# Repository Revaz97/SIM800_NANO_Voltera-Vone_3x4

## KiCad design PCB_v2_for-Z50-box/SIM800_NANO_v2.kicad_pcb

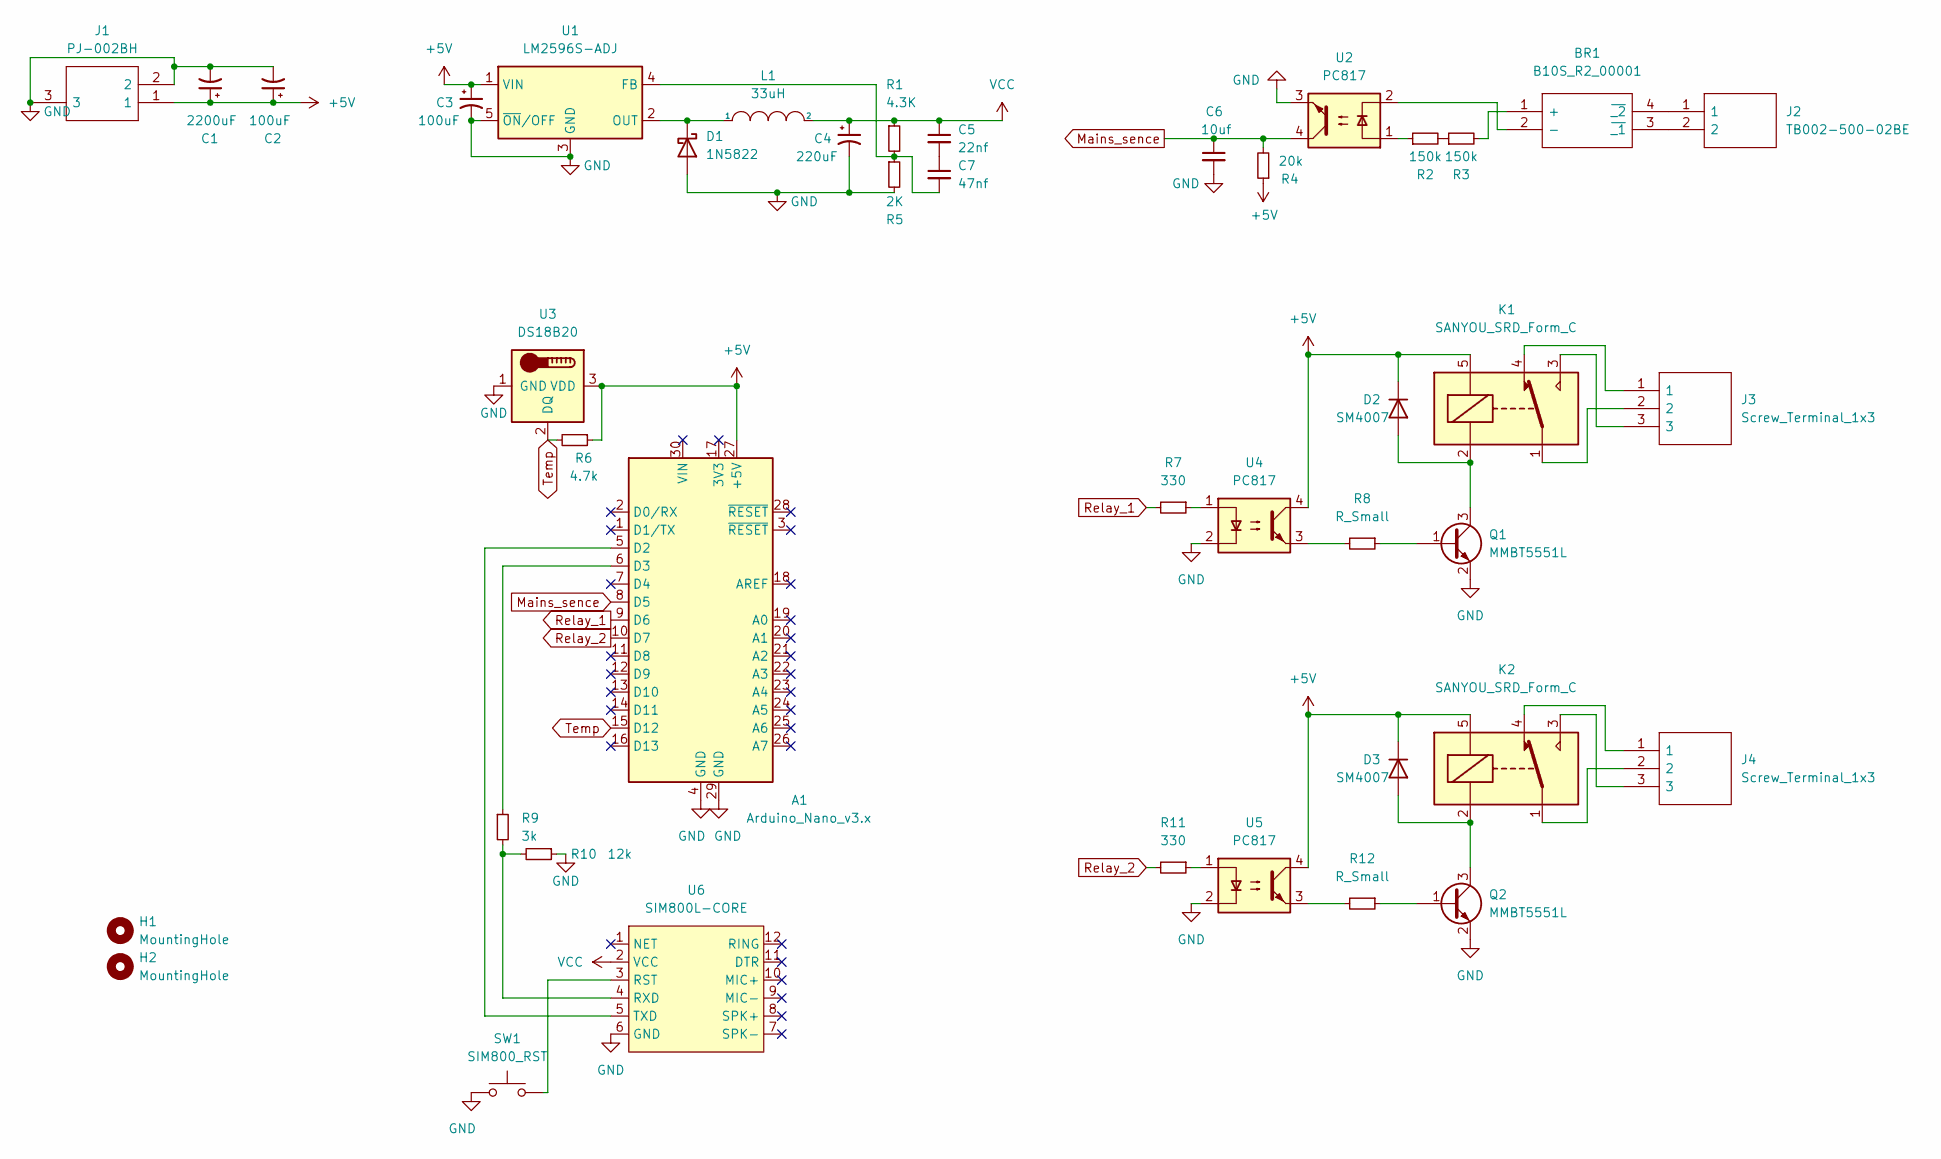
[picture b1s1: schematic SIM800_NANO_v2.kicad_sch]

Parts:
A1: Arduino_Nano_v3.x; Arduino_Nano
BR1: B10S_R2_00001; SOP250P700X290-4N; Mouser Part Number 241-B10S_R2_00001
C1: 2200uF; CP_Radial_D10.0mm_P5.00mm
C2: 100uF; CP_EIA-6032-15_Kemet-U
C3: 100uF; CP_Elec_10x10
C4: 220uF; CP_Elec_10x10
C5: 22nf; C_0805_2012Metric
C6: 10uf; C_1206_3216Metric
C7: 47nf; C_0805_2012Metric
D1: 1N5822; D_DO-201AD_P15.24mm_Horizontal
D2, D3: SM4007; D_SOD-323_HandSoldering
H1, H2: MountingHole; MountingHole_2.7mm
J1: PJ-002BH; PJ002BH; Mouser Part Number 490-PJ-002BH
J2: TB002-500-02BE; TB00250002BE; Mouser Part Number 490-TB002-500-02BE
J3, J4: Screw_Terminal_1x3; Mouser Part Number 651-1711039
K1, K2: SANYOU_SRD_Form_C; Relay_SPDT_SANYOU_SRD_Series_Form_C
L1: 33uH; L_Bourns_SRR1260
Q1, Q2: MMBT5551L; SOT-23
R1: 4.3K; R_0805_2012Metric
R2, R3: 150k; R_1206_3216Metric
R4: 20k; R_0805_2012Metric
R5: 2K; R_0805_2012Metric
R6: 4.7k; R_0805_2012Metric
R7, R11: 330; R_0805_2012Metric
R8, R12: R_Small; R_0805_2012Metric
R9: 3k; R_0805_2012Metric
R10: 12k; R_0805_2012Metric
SW1: SIM800_RST; SW_SPST_TL3305A
U1: LM2596S-ADJ; TO-263-5_TabPin3
U2, U4, U5: PC817; DIP-4_W7.62mm
U3: DS18B20; TO-92_Inline
U6: SIM800L-CORE; SIM800L

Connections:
+5V: A1.27 (+5V), C1.1, C2.1, C3.1, D2.1 (K), D3.1 (K), J1.1, K1.5, K2.5, R4.1, R6.1, U1.1 (VIN), U3.3 (VDD), U4.4, U5.4
GND: A1.4 (GND), A1.29 (GND), C1.2, C2.2, C3.2, C4.2, C6.2, D1.2 (A), J1.2, J1.3, Q1.2 (E), Q2.2 (E), R5.2, R10.1, SW1.1, U1.3 (GND), U1.5 (~ON/OFF), U2.3, U3.1 (GND), U4.2, U5.2, U6.6 (GND)
Mains_sence: A1.8 (D5), C6.1, R4.2, U2.4
unnamed: A1.5 (D2), U6.5 (TXD)
unnamed: A1.6 (D3), R9.1
unnamed: BR1.1 (+), R3.2
unnamed: BR1.2 (-), U2.2
unnamed: BR1.3 (~_1), J2.2
unnamed: BR1.4 (~_2), J2.1
unnamed: C5.2, C7.1
unnamed: C7.2, R1.2, R5.1, U1.4 (FB)
unnamed: D1.1 (K), L1.1, U1.2 (OUT)
unnamed: D2.2 (A), K1.2, Q1.3 (C)
unnamed: D3.2 (A), K2.2, Q2.3 (C)
unnamed: J3.1, K1.4
unnamed: J3.2, K1.1
unnamed: J3.3, K1.3
unnamed: J4.1, K2.4
unnamed: J4.2, K2.1
unnamed: J4.3, K2.3
unnamed: Q1.1 (B), R8.1
unnamed: Q2.1 (B), R12.1
unnamed: R2.1, U2.1
unnamed: R2.2, R3.1
unnamed: R7.1, U4.1
unnamed: R8.2, U4.3
unnamed: R9.2, R10.2, U6.4 (RXD)
unnamed: R11.1, U5.1
unnamed: R12.2, U5.3
unnamed: SW1.2, U6.3 (RST)
Relay_1: A1.9 (D6), R7.2
Relay_2: A1.10 (D7), R11.2
Temp: A1.15 (D12), R6.2, U3.2 (DQ)
VCC: C4.1, C5.1, L1.2, R1.1, U6.2 (VCC)

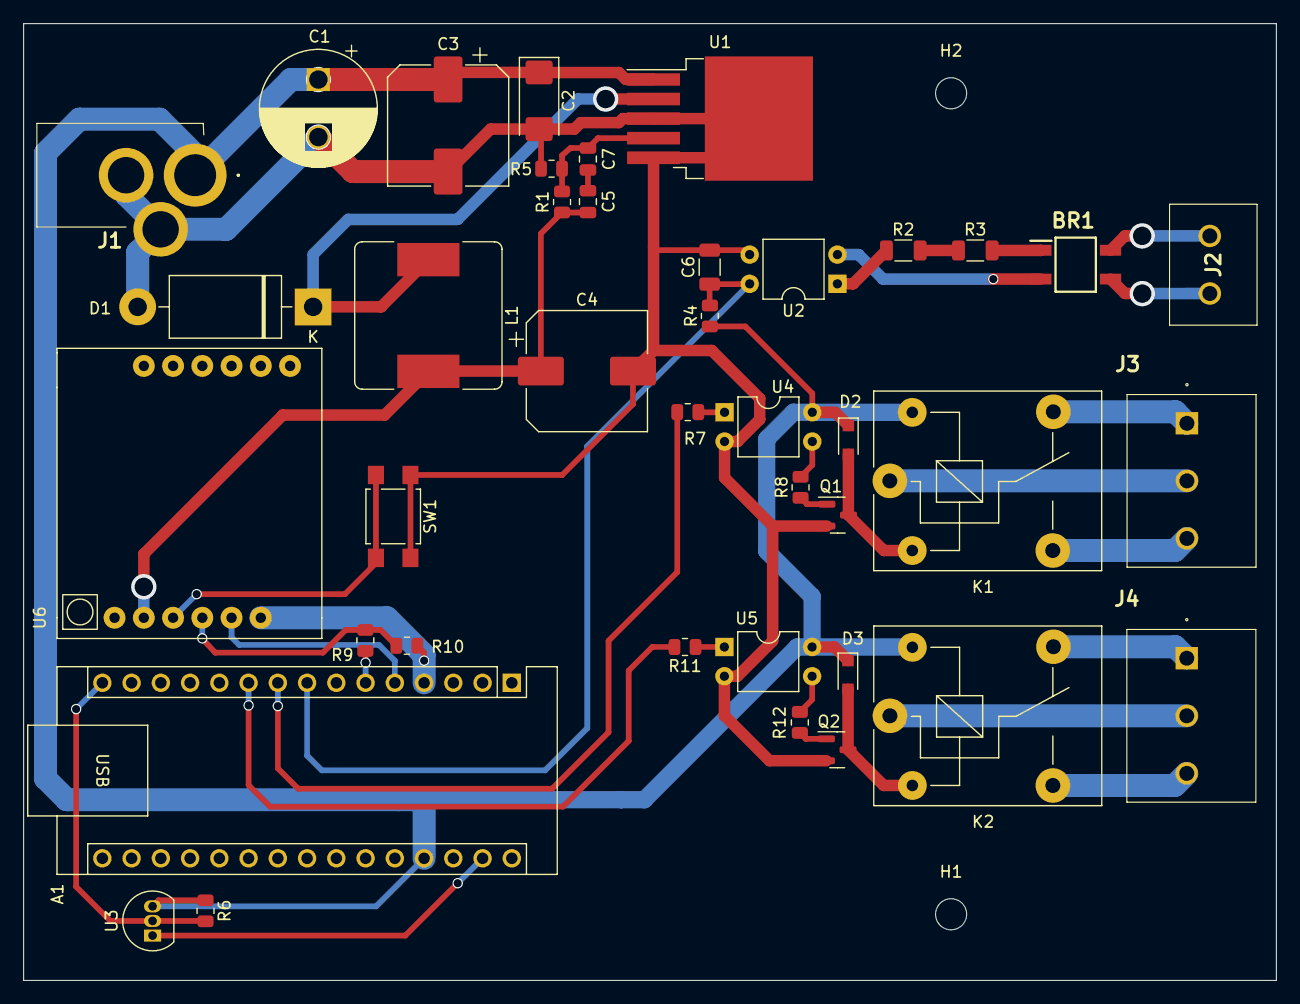
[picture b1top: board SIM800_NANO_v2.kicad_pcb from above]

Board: 2 copper layers, 108.8 x 83.1 mm, 42 parts (0 on the bottom side), 34 nets.

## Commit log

2022-12-11 Divided V1 and V2 PCBs
2022-12-12 Modified vias
2022-12-12 updated code
2022-12-23 Temp sensor pin13 to pin12
